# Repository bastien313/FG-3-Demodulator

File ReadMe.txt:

Création of project.
Demodulator for FLuxGate Sensor FGM-3

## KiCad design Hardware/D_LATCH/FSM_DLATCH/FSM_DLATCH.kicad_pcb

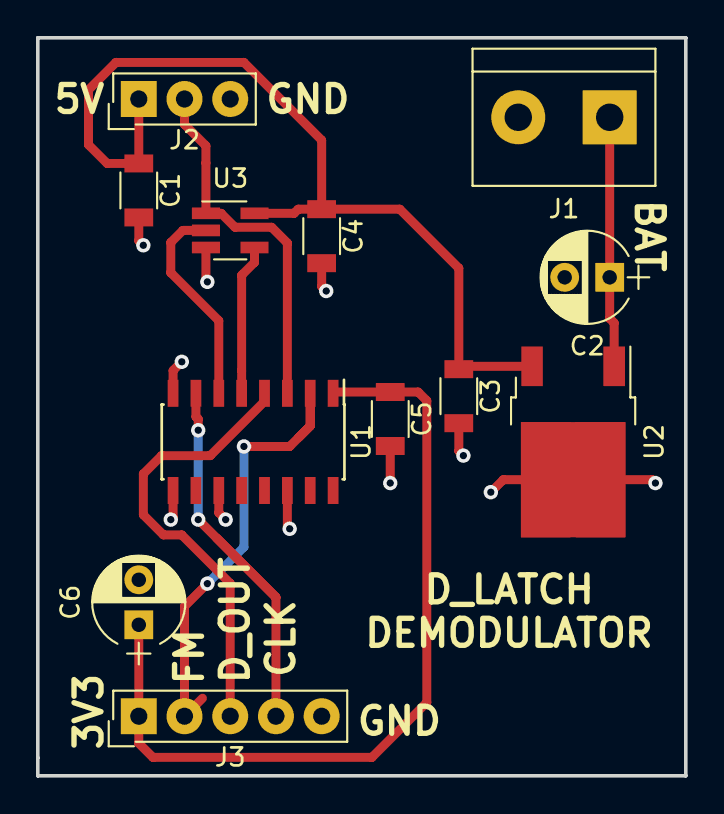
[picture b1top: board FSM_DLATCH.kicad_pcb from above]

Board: 2 copper layers, 36.0 x 41.0 mm, 12 parts (0 on the bottom side), 10 nets.

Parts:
C1, C3, C4, C5: 100nF; C_1206
C2, C6: 10uF 25V; CP_Radial_D5.0mm_P2.50mm
J1: Conn_01x02; TerminalBlock_bornier-2_P5.08mm
J2: FGM SENSOR; SL-103-X-XX_1x03
J3: Conn_01x05; SL-105-X-XX_1x05
U1: 74HC4050; SOIC-16_3.9x9.9mm_Pitch1.27mm
U2: L7805; TO-252-2
U3: 74LVC1G79; SOT-23-5_HandSoldering

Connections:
+3V3: C5.1, C6.1, J3.1, U1.1
+5V: C1.1, C3.1, C4.1, J2.1, U2.3, U3.5
+BATT: C2.1, J1.1, U2.1
/CLK_IN_UC: J3.4, U1.7
/D_OUT_UC: J3.3, U1.4
/FM_OUT: J2.2, U1.3, U3.1
/FM_OUT_UC: J3.2, U1.2
GND: C1.2, C2.2, C3.2, C4.2, C5.2, C6.2, J1.2, J2.3, J3.5, U1.8, U1.9, U1.11, U1.14, U2.2, U3.3
unnamed: U1.5, U3.4
unnamed: U1.6, U3.2

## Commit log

2019-04-20 creation
2019-04-20 Finalisation of schematic
2019-04-23 D_Latch design is finish
2019-04-23 Creation of PLL demodulator
2019-04-23 Add somme change
2019-04-27 Création of software folder
2019-04-27 création of embeded software
